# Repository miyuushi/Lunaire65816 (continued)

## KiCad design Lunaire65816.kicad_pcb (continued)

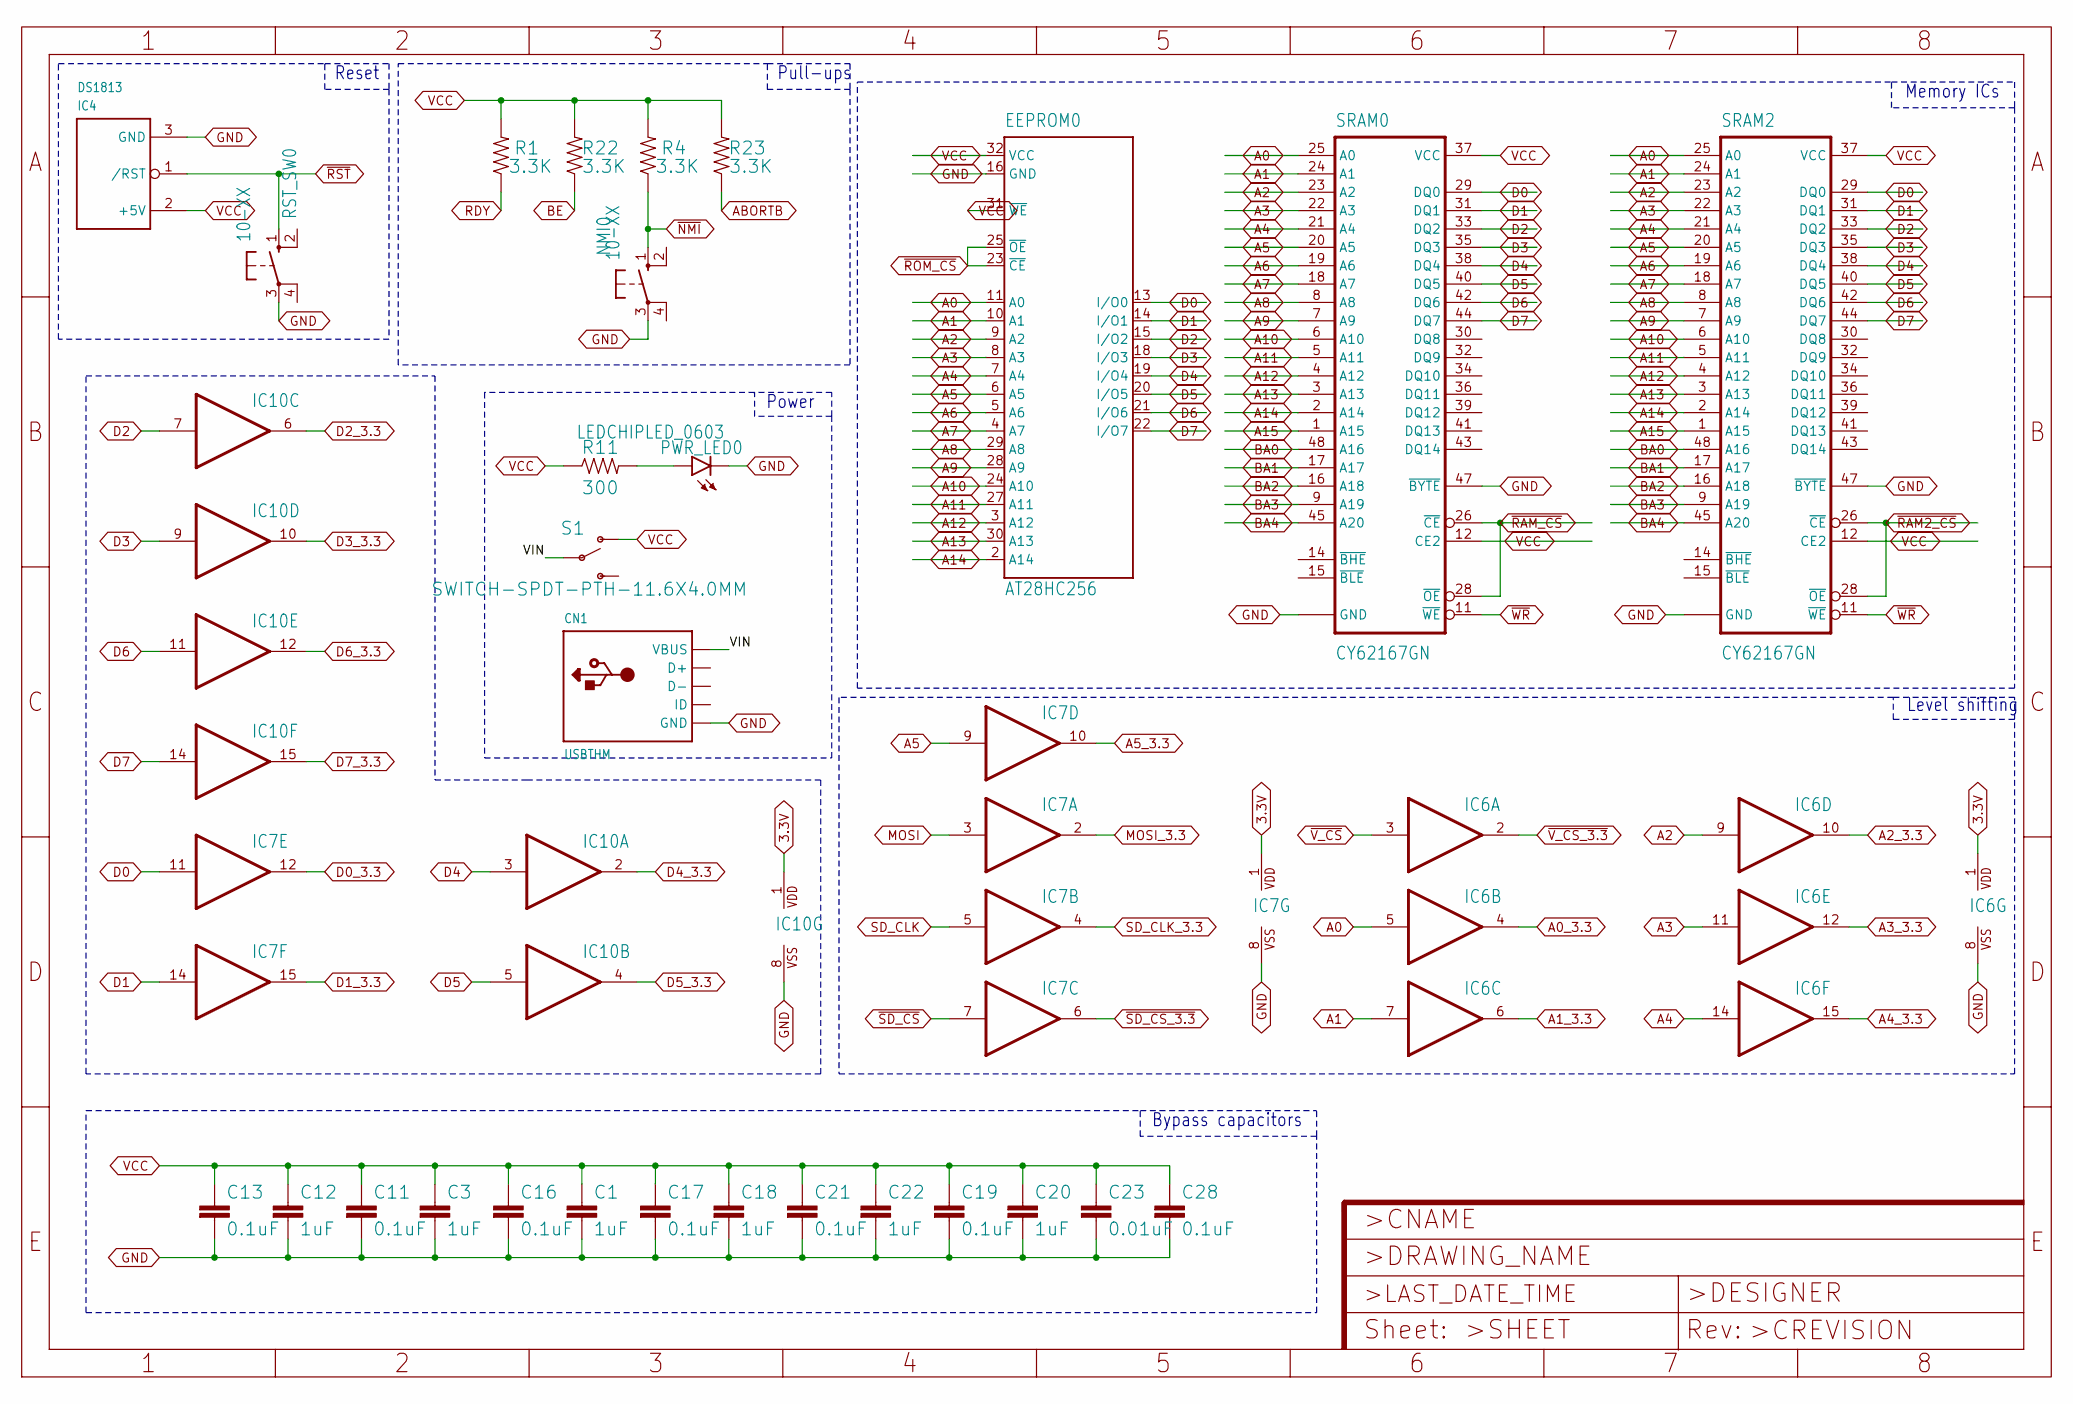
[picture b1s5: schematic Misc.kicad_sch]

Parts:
C1, C3, C12, C18, C20, C22: 1uF; 0603
C11, C13, C16, C17, C19, C21, C28: 0.1uF; 0603
C23: 0.01uF; 0603
CN1: USBTHM; USB-MINIB-THM
EEPROM0: AT28HC256; PLCC-32
IC4: DS1813; TO-92
IC6, IC7, IC10: 4050N; DIL16
NMI0: 10-XX; B3F-10XX
PWR_LED0: LEDCHIPLED_0603; CHIPLED_0603
R1, R4, R22, R23: 3.3K; 0603
R11: 300; 0603
RST_SW0: 10-XX; B3F-10XX
S1: SWITCH-SPDT-PTH-11.6X4.0MM; SWITCH_SPDT_PTH_11.6X4.0MM
SRAM0, SRAM2: CY62167GN; TSOP48

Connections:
3.3V: IC6.1 (VDD), IC7.1 (VDD), IC10.1 (VDD); also elsewhere on the board
A0: EEPROM0.11 (A0), IC6.5 (I), SRAM0.25 (A0), SRAM2.25 (A0); also elsewhere on the board
A0_3.3: IC6.4 (O); also elsewhere on the board
A1: EEPROM0.10 (A1), IC6.7 (I), SRAM0.24 (A1), SRAM2.24 (A1); also elsewhere on the board
A1_3.3: IC6.6 (O); also elsewhere on the board
A2: EEPROM0.9 (A2), IC6.9 (I), SRAM0.23 (A2), SRAM2.23 (A2); also elsewhere on the board
A2_3.3: IC6.10 (O); also elsewhere on the board
A3: EEPROM0.8 (A3), IC6.11 (I), SRAM0.22 (A3), SRAM2.22 (A3); also elsewhere on the board
A3_3.3: IC6.12 (O); also elsewhere on the board
A4: EEPROM0.7 (A4), IC6.14 (I), SRAM0.21 (A4), SRAM2.21 (A4); also elsewhere on the board
A4_3.3: IC6.15 (O); also elsewhere on the board
A5: EEPROM0.6 (A5), IC7.9 (I), SRAM0.20 (A5), SRAM2.20 (A5); also elsewhere on the board
A5_3.3: IC7.10 (O); also elsewhere on the board
A6: EEPROM0.5 (A6), SRAM0.19 (A6), SRAM2.19 (A6); also elsewhere on the board
A7: EEPROM0.4 (A7), SRAM0.18 (A7), SRAM2.18 (A7); also elsewhere on the board
A8: EEPROM0.29 (A8), SRAM0.8 (A8), SRAM2.8 (A8); also elsewhere on the board
A9: EEPROM0.28 (A9), SRAM0.7 (A9), SRAM2.7 (A9); also elsewhere on the board
A10: EEPROM0.24 (A10), SRAM0.6 (A10), SRAM2.6 (A10); also elsewhere on the board
A11: EEPROM0.27 (A11), SRAM0.5 (A11), SRAM2.5 (A11); also elsewhere on the board
A12: EEPROM0.3 (A12), SRAM0.4 (A12), SRAM2.4 (A12); also elsewhere on the board
A13: EEPROM0.30 (A13), SRAM0.3 (A13), SRAM2.3 (A13); also elsewhere on the board
A14: EEPROM0.2 (A14), SRAM0.2 (A14), SRAM2.2 (A14); also elsewhere on the board
A15: SRAM0.1 (A15), SRAM2.1 (A15); also elsewhere on the board
ABORTB: R23.1; also elsewhere on the board
BA0: SRAM0.48 (A16), SRAM2.48 (A16); also elsewhere on the board
BA1: SRAM0.17 (A17), SRAM2.17 (A17); also elsewhere on the board
BA2: SRAM0.16 (A18), SRAM2.16 (A18); also elsewhere on the board
BA3: SRAM0.9 (A19), SRAM2.9 (A19); also elsewhere on the board
BA4: SRAM0.45 (A20), SRAM2.45 (A20); also elsewhere on the board
BE: R22.1; also elsewhere on the board
D0: EEPROM0.13 (I/O0), IC7.11 (I), SRAM0.29 (DQ0), SRAM2.29 (DQ0); also elsewhere on the board
D0_3.3: IC7.12 (O); also elsewhere on the board
D1: EEPROM0.14 (I/O1), IC7.14 (I), SRAM0.31 (DQ1), SRAM2.31 (DQ1); also elsewhere on the board
D1_3.3: IC7.15 (O); also elsewhere on the board
D2: EEPROM0.15 (I/O2), IC10.7 (I), SRAM0.33 (DQ2), SRAM2.33 (DQ2); also elsewhere on the board
D2_3.3: IC10.6 (O); also elsewhere on the board
D3: EEPROM0.18 (I/O3), IC10.9 (I), SRAM0.35 (DQ3), SRAM2.35 (DQ3); also elsewhere on the board
D3_3.3: IC10.10 (O); also elsewhere on the board
D4: EEPROM0.19 (I/O4), IC10.3 (I), SRAM0.38 (DQ4), SRAM2.38 (DQ4); also elsewhere on the board
D4_3.3: IC10.2 (O); also elsewhere on the board
D5: EEPROM0.20 (I/O5), IC10.5 (I), SRAM0.40 (DQ5), SRAM2.40 (DQ5); also elsewhere on the board
D5_3.3: IC10.4 (O); also elsewhere on the board
D6: EEPROM0.21 (I/O6), IC10.11 (I), SRAM0.42 (DQ6), SRAM2.42 (DQ6); also elsewhere on the board
D6_3.3: IC10.12 (O); also elsewhere on the board
D7: EEPROM0.22 (I/O7), IC10.14 (I), SRAM0.44 (DQ7), SRAM2.44 (DQ7); also elsewhere on the board
D7_3.3: IC10.15 (O); also elsewhere on the board
GND: C1.2, C3.2, C11.2, C12.2, C13.2, C16.2, C17.2, C18.2, C19.2, C20.2, C21.2, C22.2, C23.2, C28.2, CN1.GND, EEPROM0.16 (GND), IC4.3 (GND), IC6.8 (VSS), IC7.8 (VSS), IC10.8 (VSS), NMI0.3, PWR_LED0.C, RST_SW0.3, SRAM0.27 (GND), SRAM0.46 (GND), SRAM0.47 (~BYTE), SRAM2.27 (GND), SRAM2.46 (GND), SRAM2.47 (~BYTE); also elsewhere on the board
MOSI: IC7.3 (I); also elsewhere on the board
MOSI_3.3: IC7.2 (O); also elsewhere on the board
unnamed: PWR_LED0.A, R11.2
RDY: R1.1; also elsewhere on the board
SD_CLK: IC7.5 (I); also elsewhere on the board
SD_CLK_3.3: IC7.4 (O); also elsewhere on the board
VCC: C1.1, C3.1, C11.1, C12.1, C13.1, C16.1, C17.1, C18.1, C19.1, C20.1, C21.1, C22.1, C23.1, C28.1, EEPROM0.31 (~WE), EEPROM0.32 (VCC), IC4.2 (+5V), R1.2, R4.2, R11.1, R22.2, R23.2, S1.1 (O), SRAM0.12 (CE2), SRAM0.37 (VCC), SRAM2.12 (CE2), SRAM2.37 (VCC); also elsewhere on the board
VIN: CN1.VBUS, S1.2
~NMI: NMI0.1 (S), R4.1; also elsewhere on the board
~RAM2_CS: SRAM2.26 (~CE), SRAM2.28 (~OE); also elsewhere on the board
~RAM_CS: SRAM0.26 (~CE), SRAM0.28 (~OE); also elsewhere on the board
~ROM_CS: EEPROM0.23 (~CE), EEPROM0.25 (~OE); also elsewhere on the board
~RST: IC4.1 (/RST), RST_SW0.1 (S); also elsewhere on the board
~SD_CS_3.3: IC7.6 (O); also elsewhere on the board
~SD_CS: IC7.7 (I); also elsewhere on the board
~V_CS_3.3: IC6.2 (O); also elsewhere on the board
~V_CS: IC6.3 (I); also elsewhere on the board
~WR: SRAM0.11 (~WE), SRAM2.11 (~WE); also elsewhere on the board

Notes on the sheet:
Memory ICs
Reset
Level shifting
Power
Bypass capacitors
Pull-ups

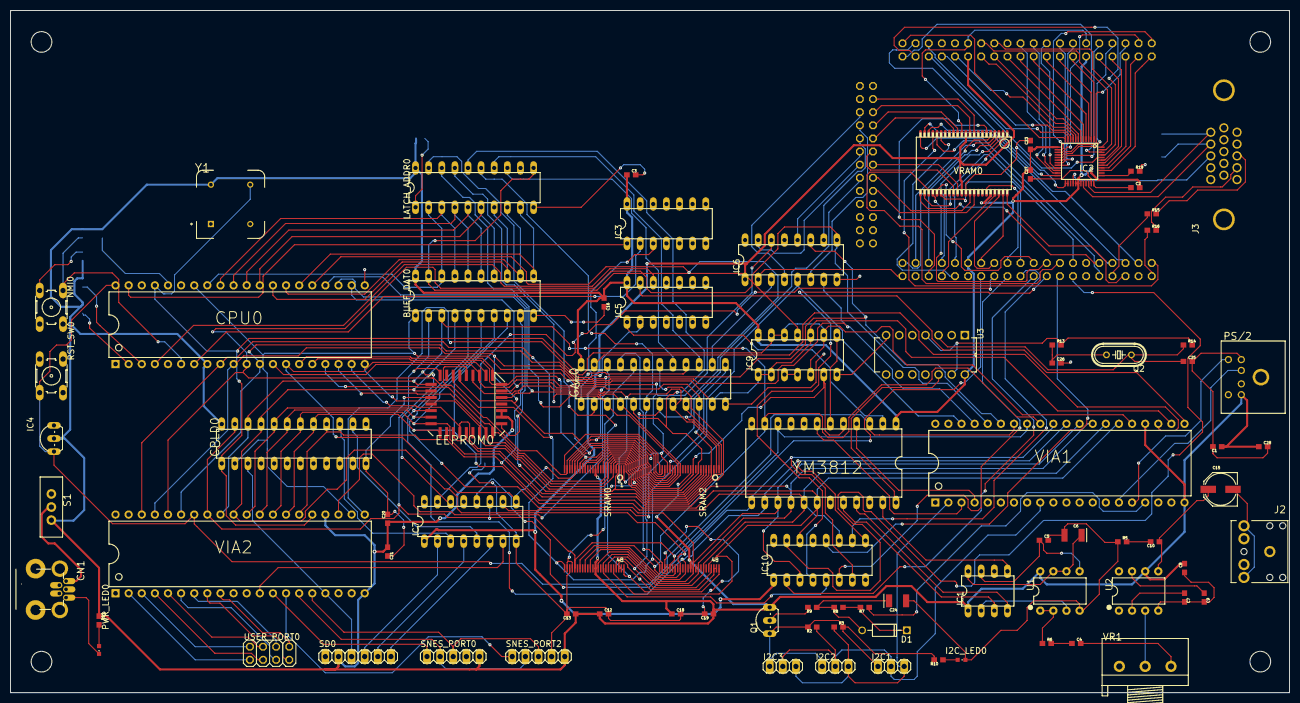
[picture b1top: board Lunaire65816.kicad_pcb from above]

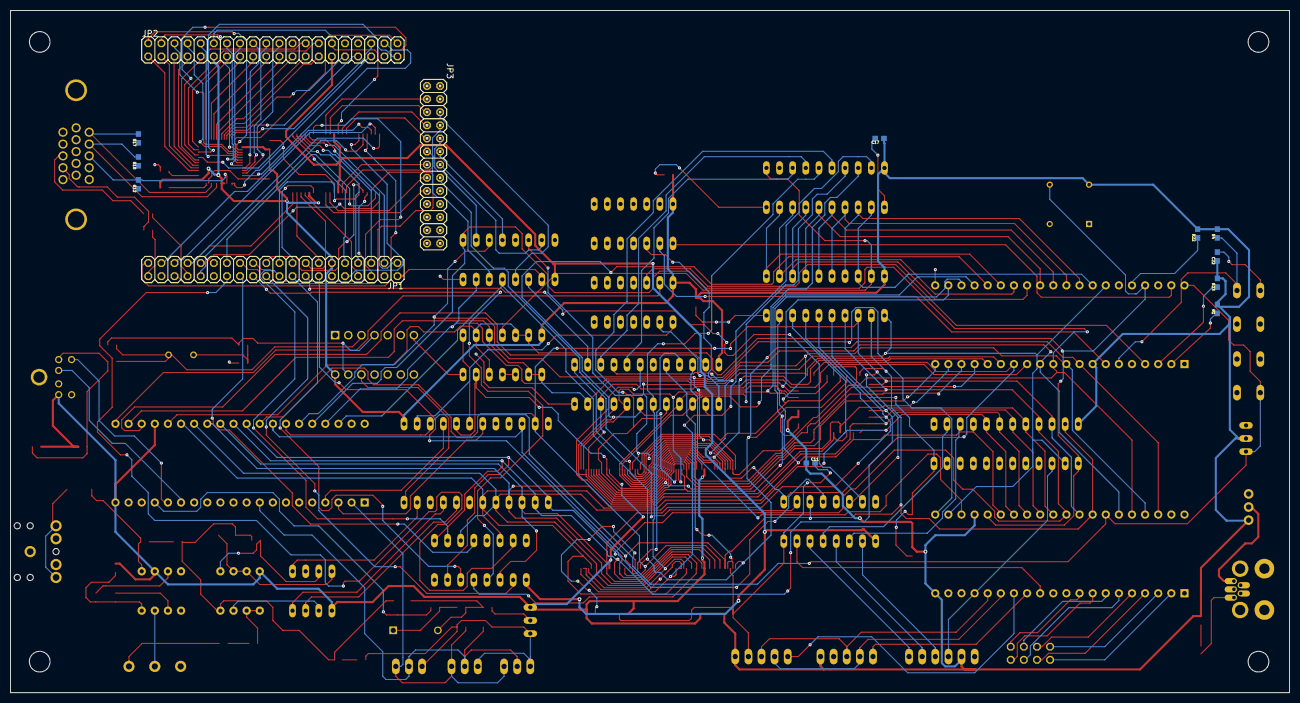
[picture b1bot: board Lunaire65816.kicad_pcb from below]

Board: 2 copper layers, 247.7 x 132.1 mm, 100 parts (13 on the bottom side), 209 nets.

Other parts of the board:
@HOLE0, @HOLE1, @HOLE2, @HOLE3: (no value)

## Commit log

2026-04-01 Initial
2026-04-10 Add license and readme
